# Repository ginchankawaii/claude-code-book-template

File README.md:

# 🧪 ENCOR合格ストーリー 〜タキと目指す9月合格〜

CCNP ENCOR(350-401)に**2026年9月(上期末)合格**するための、ギャルゲー風・学習継続アプリです。
毎日の勉強を記録すると、検証ラボの同期・**早瀬タキ**(ツンデレ天才研究者)の好感度が上がり、レベルアップでイベントが発生。合格報告でハッピーエンドを迎えます。

> タキ『べ、別にキミのためにこのアプリがあるわけじゃないんだからね。……データが欲しいだけさ』

## 📱 iPhoneにアプリとして入れる方法(PWA)

このアプリはPWA対応済みなので、ホーム画面に追加すると**普通のアプリと同じように全画面・オフラインで動きます**。

1. このリポジトリをGitHub Pagesで公開する(初回のみ)
   - GitHubの **Settings → Pages → Branch: main → Save**
   - 数分後に `https://<ユーザー名>.github.io/<リポジトリ名>/` でアクセスできるようになる
2. iPhoneの**Safari**でそのURLを開く
3. **共有ボタン(□↑) → 「ホーム画面に追加」**
4. ホーム画面にタキのアイコンが追加される → 以降はアプリとして起動🧪

データはブラウザ(ホーム画面アプリ)内に保存されます。月1回「データ書き出し」でJSONバックアップ推奨。

※PCで使う場合は `index.html` をダブルクリックするだけでも動きます。

## 🎮 ゲームシステム

| 要素 | 内容 |
|---|---|
| 好感度 (0〜100) | 毎日の記録で上昇。30分以上・40問以上・正答率80%以上・7日連続でボーナス |
| レベル | Lv.1 観察対象 → Lv.2 共同研究者 → Lv.3 興味深いキミ → Lv.4 かけがえのない相棒 → Lv.5 運命共同体(たぶん) |
| イベント | レベルアップ時・連続7/14/30日達成時に特別イベント発生 |
| 表情 | ドット絵4表情: ニヤリ(通常)・デレ・キラキラ・ツン(サボると拗ねる) |
| キャラ差し替え | 好きな二次元画像(生成AI画像など)をキャラとして設定可能 |
| 復帰歓迎 | 3日以上サボっても「心配なんかしてない」と言いながら迎えてくれます |
| ハッピーエンド | 「合格しました!!」ボタンでツンデレ告白エンド 🌸(下期ENARSI編に続く) |

## 👩‍🔬 早瀬タキ(はやせ・タキ)

会社の検証ラボに入り浸る同期の天才エンジニア。白衣・栗色の乱れ髪・深紅の目・胸ポケットに試験管。
一人称「私」、キミ呼び。勉強を「実験」、記録を「データ提出」と呼ぶ。素直じゃないが、誰よりもキミの合格を信じている。

**キャラはドット絵(4表情)で描画されます。** もっと可愛くしたい場合は「🖼 キャラ画像に差し替え」ボタンで、
生成AI(にじジャーニー等)で作った画像や好きな二次元画像に差し替えられます(画像は端末内にのみ保存)。

## 📖 ドキュメント

- [docs/study-plan.md](docs/study-plan.md) — 7〜9月の週次学習計画・1日のルーチン・if-thenルール・モチベーション維持の仕組み
- [docs/simulation.md](docs/simulation.md) — ENCORシミュレーション(ラボ)問題の対策メモ・頻出設定テーマ・本番の立ち回り
- [docs/ipoe-lab/](docs/ipoe-lab/README.md) — PPPoE→IPoE切替検証ラボ(VMware)の設計・構築手順・検証マトリクス(業務用)

## 🗺️ 合格までのロードマップ

```
7月         8月         9月
├─ 銀メダル化 ─┼─ 金メダル化 ─┼─ 模試+シミュ対策 ─→ 🌸受験🌸
   (二周目)     (+コマ問)      (85〜90%安定で予約)
```

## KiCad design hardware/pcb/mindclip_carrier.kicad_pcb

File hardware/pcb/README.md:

# MindClip DIY — 基板（PCB）設計

**結論から: v1 では基板を作らない。** 4案を設計・比較し、3人の審査員が独立採点した結果、
**「基板を起こさず、空中配線を改良する」案が採用**された。ただし検討は無駄にならず、
v1 の設計が **はんだ11点 → 10点** に減り、**電池の極性事故リスクが下がった**（JSTコネクタ化）。
（v1.8 rev2〜v1.10 ではピグテールの線を細い AWG28 に継ぎ足す 2点があり 12点だったが、採用ピグテールの線は実測 0.90mm と細く
そのまま使えるため v1.11 で廃止した。**現在の作業は 10点（線が太いピグテールで継ぎ足す場合のみ +2）**。
電池側のコネクタは **1.25mm ピッチ 2P** と確定した。正本は [`SCHEMATIC.md`](SCHEMATIC.md) §0.1 / §1.4。）
**v2用の基板 2種（MC-SENSE-A / MC-CARRIER-A）は、現在の筐体（v1.8、内寸幅 36.8mm・実測スイッチ）には
どちらも合わず、筐体 CAD でも実行できない**（[`LAYOUT.md`](LAYOUT.md) §0 冒頭）。
将来 v2 で基板が必要になったときのために、**発注可能な基板データも作って置いてある**。

- 採用構成の詳細 → [`SCHEMATIC.md`](SCHEMATIC.md)（回路・ネットリスト・テスタゲート）
- v2用の基板データ → [`LAYOUT.md`](LAYOUT.md) §0 を**必ず先に読むこと**
- 組み立て手順 → [`../README.md`](../README.md)

---

## 1. なぜ基板を作らないのか

### 1.1 高さ予算が足りない

筐体CAD（`../cad/mindclip_case.py`）を実行して実測した、基板を入れられる余地:

| バリアント | 高さ予算 | 1.6mm厚基板 | 0.8mm厚基板 |
|---|---|---|---|
| allday | **2.30 mm** | 入る（ただし余裕0.7mm） | 入る |
| slim | **0.60 mm** | **入らない** | **入らない**（はんだフィレット+固定材で超過） |

**slim バリアントは、どんな基板を入れても原理的に成立しない。** 基板を採用すると
2バリアント体制を捨てるか、筐体を作り直すことになる。

### 1.2 寸法がまだ実測されていない

より本質的な理由。`../README.md` §9.1 に列挙した**未検証の寸法が1つも実測されていない**:

- XIAOスタックの総厚 **7.5mm（assumption）** ← slim の内寸9.5mmはこの値に直接依存
- マイクの基板上の位置、XIAO裏面BATパッドの正確な位置
- 802530電池の実寸、USB-Cケーブルの嵌合

もし実測でスタック厚が 8.3mm だったら、slim の内寸は即破綻する。
**基板は「寸法が固まった後の最適化」であって、「寸法を固める手段」ではない。**
この状態で基板を焼くと、失敗コストが「2週間の納期 + ¥4,700 + XIAO ¥2,660」になる。

### 1.3 反復コストの差

| | 設計ミスに気づいてから直るまで |
|---|---|
| 空中配線 | **その晩**（線を1本付け替える） |
| 基板 | **2週間**（再発注） |

ファームウェアがまだ存在せず、VBUS検出のGPIO選定・分圧比・ADC校正を
「回路を触りながら詰める」段階では、この差が決定的に効く。

---

## 2. 4案の比較

| | 案A **採用** | 案B | 案C | 案D |
|---|---|---|---|---|
| 構成 | 基板なし・空中配線改良 | キャリア基板（直はんだ） | キャリア基板＋ソケット | ユニバーサル基板手組み |
| 追加高さ | **0 mm** | +1.0 mm | **+7.1 mm** | 0 mm |
| 手はんだ | **10点** | 20点 | **54点** | 36点 |
| 費用 | ¥1,100 | ¥4,700 | ¥1,400 | ¥310 |
| 納期 | **即日** | 2週間 | 3週間 | 即日 |
| VBUS検出 | ✗ | ✓ | ✓ | ✓ |
| 電池監視 | ✗ | ✓ | ✓ | ✓ |
| 採点合計 | **174** | 132 | 42 | 79 |

審査員の推し: 組立性→**案A** / 機構→**案A** / 電気→**案B**

### 不採用の理由

- **案B（キャリア基板）**: 設計としては最も筋が良く、**v2 で作るならこれ**。
  ただし今作ると 1.2 の「寸法未実測」に直撃する。また目的の一つだった
  「電池直はんだの排除」は達成できない（BATパッドが基板裏面にあるため窓＋ジャンパが残る）。
  手はんだも 11→20点と**増える**。
- **案C（ソケット式）**: 却下。外形が +4.6mm（14.6→19.2mm）、手はんだ54点、slim消滅。
  「XIAOを壊しても差し替えられる」という唯一の価値も、BAT+/−がヘッダに出ていないため
  成立しない。**予備のXIAOを1枚買う（¥2,660・即日）ほうが安くて確実。**
- **案D（ユニバーサル基板）**: 「まず1台試す」段階の現実解ではあるが、
  再現性とドキュメント化に耐えない（24穴中19穴に詰め込み、手はんだ36点）。

---

## 3. 検討の結果、v1 に反映されたこと

基板を作らないと決めた一方で、**案Aの改良（A-1）は v1 に取り込んだ**:

| | 変更前 (v1) | 変更後 (v1.5) |
|---|---|---|
| 電池の接続 | BATパッドに**直はんだ** | **JST ピグテール**（コネクタ嵌合。電池側プラグと同じ **1.25mm ピッチ 2P**。当初の「PH2.0」指定は誤りで訂正済み） |
| GND配線 | 空中で3本より合わせ（スプライス） | **デイジーチェーン**（スプライス廃止） |
| はんだ点数 | 11点 | **10点**（線が太いピグテールで継ぎ足す場合のみ +2。v1.8 rev2〜v1.10 は継ぎ足しが標準で 12点だった） |
| 電池リード長 | 未指定 | ピグテールを根元から約 60 / 65mm の長さ違いに切ってそのまま使う（v1.11。v1.5 時点は「40mm 指定」、v1.8 rev2〜v1.10 は「10 / 15mm で切って AWG28 55mm を継ぐ」） |

**JSTコネクタ化の効果**: 電池を「挿す」作業に変わるので、はんだごてを持ったまま
極性を間違える事故が減る。加えて、電池だけ後から外せるので保管・輸送も安全になる。

> **ただし極性リスクはゼロにならない。** JSTの極性キーは「上下逆挿し」しか防がず、
> **ハウジング内のコンタクト位置が逆に配線された電池（中華セルに実在）は防げない**。
> `SCHEMATIC.md` §5.4 の**嵌合前テスタゲートは必須のまま**。組立ガイドの手順8に
> 「リード線の色を信用せず、コンタクト位置で極性を測る」手順として組み込んである。

---

## 4. v2用の基板データ（発注しないこと）

将来のために、2種類の基板を設計してガーバーまで出力してある。

| 基板 | 外形 | 用途 |
|---|---|---|
| `mindclip_sense.kicad_pcb` | 10.0 × 15.6 mm | サテライト基板。VBUS検出＋電池監視だけを載せる最小構成 |
| `mindclip_carrier.kicad_pcb` | 34.2 × 21.5 mm | キャリア基板。XIAOをカステレーション直はんだ |

**発注してよいのは、以下のゲートを全て通過してからである**（`SCHEMATIC.md` §9.4）:

1. v1 を1台組んで、消費電流ゲート（平均 ≤28mA）を通す
2. **ノギスでXIAOスタック総厚を実測**し、`XIAO_STACK_T` を更新
3. XIAO裏面 BAT+/− パッドの座標を実測
4. 802530の実寸・リード出射方向・JSTプラグ極性を確認
5. `gen_pcb.py` を再実行して DRC を通す

### 検証状況（正直に）

- ✅ 独立ジオメトリDRC **エラー0件**。設計途中で見つかった**異ネット衝突41件
  （うち銅箔レベルの直短絡16件）は修正済み**で、独立検証でも0件を確認した
- ❌ **KiCad本体のDRCは一度も走っていない**（この環境にKiCadが無いため）
- ❌ 製造業者のDFMチェックも未実施
- ❌ 逆接続保護FETは MC-CARRIER-A rev.A には**載っていない**

発注前に必ず KiCad で開いて DRC を通すこと（手順は `LAYOUT.md` §9.3）。

---

## 5. 基板を作るべき条件

以下のどれかに当てはまったら、案B（キャリア基板）に移行する:

1. 実測でXIAOスタック厚が 7.5mm を明確に**下回った**（高さ予算に余裕ができる）
2. **3台以上作る** / 他人に作らせる / 書籍の作例にする
3. **VBUS検出**（充電開始をトリガに自動同期）が必須要件に昇格した
4. 極性ミスによる破損を**設計で排除する**ことが要件になった

3番は全体設計書の「充電ドックに置いたら同期開始」に対応する。
v1 ではこの回路が無いため、**同期のトリガはスライドスイッチOFFのみ**である。

---

## 6. ファイル一覧

| ファイル | 内容 |
|---|---|
| `SCHEMATIC.md` | 回路設計・ネットリスト・テスタゲート（**採用案A-1の正本**） |
| `LAYOUT.md` | 基板レイアウト仕様・製造仕様・発注手順 |
| `OPTION_A〜D_*.md` | 4案それぞれの詳細検討 |
| `netlist.json` | 機械可読ネットリスト |
| `gen_pcb.py` | ネットリストから `.kicad_pcb` とガーバーを生成 |
| `schematic.svg` / `layout.png` | 回路図・部品配置図 |
| `gerber/` | 製造用データ（**ゲート通過前は発注不可**） |

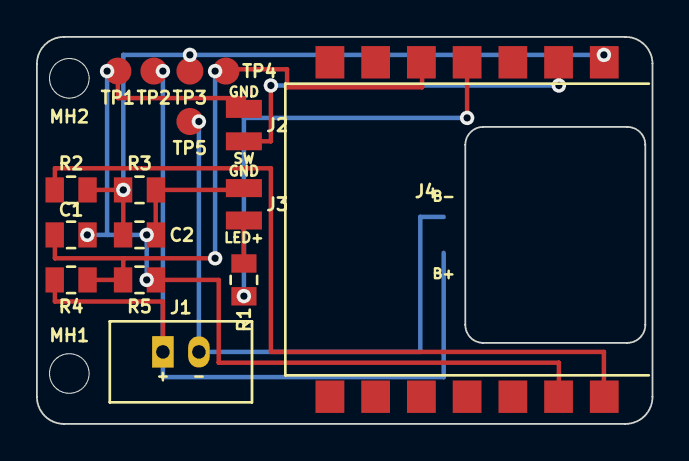
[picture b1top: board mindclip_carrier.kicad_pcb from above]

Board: 2 copper layers, 34.2 x 21.5 mm, 19 parts (0 on the bottom side), 9 nets.

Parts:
C1, C2: 100nF; C_0805_2012Metric_MC
J1: JST_PH_2P; JST_PH_B2B-PH-K_1x02_P2.00mm_Vertical_MC
J2, J3, J4: WIRE x2; WireLand_SMD
MH1, MH2: MountingHole_2.2mm; MountingHole_2.2mm_M2_MC
R1: 220R; R_0805_2012Metric_MC
R2, R4, R5: 220k; R_0805_2012Metric_MC
R3: 330k; R_0805_2012Metric_MC
TP1, TP2, TP3, TP4, TP5: TP; TestPoint_Pad_D1.5mm_MC
U1: XIAO ESP32S3 Sense; XIAO_ESP32S3_Castellated_2x7_P2.54mm

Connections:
BATN: J1.2, J4.2, TP5.1
BATP: J1.1, J4.1, R4.1, TP2.1
GND: C1.2, C2.2, J2.2, J3.2, R3.2, R5.2, TP1.1, U1.GND
LED_A: J3.1, R1.2
LED_DRV: R1.1, U1.D3
SW_IN: J2.1, U1.D1
VBAT_SENSE: C1.1, R4.2, R5.1, TP4.1, U1.D4
VBUS: R2.1, U1.5V
VBUS_SENSE: C2.1, R2.2, R3.1, TP3.1, U1.D0

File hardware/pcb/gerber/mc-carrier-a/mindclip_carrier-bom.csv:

Comment,Designator,Footprint,LCSC Part #
"100nF","C1,C2","MindClip:C_0805_2012Metric_MC",
"220R","R1","MindClip:R_0805_2012Metric_MC",
"220k","R2,R4,R5","MindClip:R_0805_2012Metric_MC",
"330k","R3","MindClip:R_0805_2012Metric_MC",
"JST_PH_2P","J1","MindClip:JST_PH_B2B-PH-K_1x02_P2.00mm_Vertical_MC",
"WIRE x2","J2,J3,J4","MindClip:WireLand_SMD",
# LCSC Part # は未指定。JLCPCB の SMT 実装を使う場合は発注前に記入すること。
# 本プロジェクトの既定は手はんだ（0805 まで）なので実装サービスは任意。

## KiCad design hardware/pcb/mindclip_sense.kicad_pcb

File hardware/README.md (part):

# MindClip DIY — 組み立てガイド（電子工作がはじめての人向け）

自作ウェアラブル音声ロガー **MindClip DIY** のハードウェアを、
**電子工作がまったく未経験の人でも、この手順どおりにやれば組める**ように書いたガイドです。

> **この文書が「正」です。** `ELECTRICAL.md` / `MECHANICAL.md` / `bom.md` と食い違いがある場合は
> このREADMEの記述を優先してください（矛盾していた箇所は各ファイル側も修正済みです）。

---

## 目次

1. [これは何か](#1-これは何か)
2. [完成品の外観](#2-完成品の外観)
3. [バリアントの選び方](#3-バリアントの選び方)
4. [必要な工具一覧](#4-必要な工具一覧)
5. [部品の購入](#5-部品の購入)
6. [3Dプリント手順](#6-3dプリント手順)
7. [組み立て手順](#7-組み立て手順)
8. [動作確認](#8-動作確認)
9. [既知の課題・未検証事項](#9-既知の課題未検証事項)

---

## 0. 最初に読む安全上の注意

作業を始める前に、これだけは頭に入れてください。

- **リチウムポリマー（LiPo）電池は、ショート・逆接続・穴あけで発火します。** 必ず保護回路（PCM）付きを買い、
  被覆を剥いた＋と−のリード線を絶対に触れ合わせないでください（[§7 手順8](#手順8-電池をつなぐjstコネクタ-最重要)）。
- **電池の極性を間違えると、XIAO（¥2,660）は一瞬で壊れます。** 復旧できません。
  v1.5 では電池を **JST コネクタ（電池に付いているプラグと同じ 1.25mm ピッチ 2ピン）で嵌合**する方式に変えましたが、
  **コネクタは「上下逆挿し」しか防いでくれません**（中身の赤黒が逆の個体、
  ハウジング内のコンタクト位置が逆の個体が実在します）。
  **嵌合の前に、テスターで4項目を確認する手順（手順8-B）が唯一の防御です。省略しないでください。**
- **電池のプラグの穴に、テスターの棒・針金・クリップなどの金属を差し込まないでください。**
  1.25mm ピッチのコンタクトは隣どうしが 1mm も離れておらず、金属が斜めに入っただけでショートします。
  電池側の電圧を測るときは、必ず**予備のピグテールを挿して、その線の先で測ります**（[手順5](#手順5-電池ピグテールjstの準備と極性の測定はんだ-0か所)・手順8-B）。
- **電池が繋がっている間は、被覆を剥いた電線の先を2本同時に自由にしない。**
  1本ずつテープで包むか、2本を3cm以上離して机にテープで留めてから作業します。
- はんだごてのこて先は **300℃以上**です。触れると重度のやけどをします。使わないときは必ずこて台に置く。
- はんだの煙は吸わない。**必ず換気**してください（窓を開ける、換気扇を回す）。
- 完成後、**microSDカードやクレジットカード・磁気定期券と密着させて持ち歩かない**でください
  （本機は背面にネオジム磁石を内蔵しています）。

---

## 1. これは何か

MindClip DIY は、襟元にクリップで留めて日常会話を録音し、
そのデータを**自宅のローカルサーバだけ**で文字起こし・要約して Obsidian の Daily Note に貯める、
「外部クラウドに一切データを出さない」音声ライフログデバイスの**自作ハードウェア（Phase 1）**です。
心臓部は Seeed Studio の小型マイコンボード **XIAO ESP32S3 Sense**（マイクとmicroSDスロットが載った拡張ボード付き）で、
外付け部品は **電池・スライドスイッチ・LED（+抵抗）の3つだけ**、はんだ付けは**合計10か所**です
（v1.5 で電池を JST コネクタ化し、空中での3本より合わせを廃止しました。
採用したコネクタ付きコードの線は細く、そのまま使えます。線が太い別のコードで継ぎ足す場合のみ +2か所）。
システム全体の考え方は [`../docs/local-llm-voice-logger-design.md`](../docs/local-llm-voice-logger-design.md)、
すでに動いている録音ファイル→Obsidian のパイプライン（Phase 0）は [`../voice-logger/`](../voice-logger/) にあります。
**このデバイスのファームウェアは実装済みです** → [`../firmware/`](../firmware/README.md)
（書き込み・WiFi設定・実測ゲートの手順はそちらのガイドにあります）。
本ガイドのゴールは「筐体と回路が正しく組み上がり、マイク・SD・スイッチ・LEDが動くことを確認したうえで、
[§8](#8-動作確認) でファームを焼いて録音〜サーバ同期まで通す」ところまでです。

---

## 2. 完成品の外観

以下は CAD（[`cad/mindclip_case.py`](cad/mindclip_case.py)）が自動生成したレンダリング画像です
（**allday バリアント**のもの。slim は [`renders/slim/`](renders/slim/) にあります）。

| 組み立て状態 | 分解図 |
|---|---|
|  |  |
| 服を挟んで、本体（手前）と裏板（服の内側）を磁石でクランプする | 上から リッド / 本体 / 磁石2個 / 裏板 / 磁石2個 |

| 三面図（寸法入り） | 内部レイアウト |
|---|---|
|  |  |
| 上面にマイク穴とスイッチ、右側面にUSB-C | 下段に電池、上段にXIAO、左にスイッチとLED |

- [`renders/allday/assembled.png`](renders/allday/assembled.png)
- [`renders/allday/exploded.png`](renders/allday/exploded.png)
- [`renders/allday/views.png`](renders/allday/views.png)
- [`renders/allday/internal.png`](renders/allday/internal.png)

配線の全体像は [`wiring.svg`](wiring.svg)（ブラウザで開いてください）が一番わかりやすいです。
**印刷して手元に置きながら作業する**ことを強く勧めます。

---

## 3. バリアントの選び方

筐体CADは **allday** と **slim** の2種類を出力できます。違いは**電池の厚みと、それに伴う筐体の奥行きだけ**です。
回路・配線・はんだ付け・部品点数は完全に同じです。

### allday（既定・**こちらを推奨**）

| 項目 | 値 |
|---|---|
| 電池 | **LiPo 802530（3.7V 680mAh、実測 32.0×25.0×8.0mm・11g、保護回路付き、コネクタは 1.25mm ピッチ 2ピン。採用品: HXJNLDC、[`bom.md`](bom.md) #2）** |
| 外形 | **40.0 × 49.4 × 14.6 mm**（v1.8 実測反映） |
| 印刷部品の重量 | 15.9 g（body 8.2 / lid 4.8 / backplate 2.9） |
| デバイス総重量 | **約35 g**（電池は実測 11g。[§9](#9-既知の課題未検証事項)の注記も参照） |
| 素の状態（省電力実装なし）の連続録音 | **約10.6時間** |
| 生成コマンド | `python3 cad/mindclip_case.py` |

### slim

| 項目 | 値 |
|---|---|
| 電池 | LiPo 502530（3.7V 500mAh、30×25×5.0mm、保護回路付き） |
| 外形 | **40.0 × 49.4 × 13.7 mm**（v1.11 実測反映） |
| 印刷部品の重量 | 15.7 g（body 7.9 / lid 5.0 / backplate 2.9） |
| デバイス総重量 | 約34 g（電池を公称 10g とした見積） |
| 素の状態（省電力実装なし）の連続録音 | 約7.8時間 |
| 生成コマンド | `MINDCLIP_VARIANT=slim python3 cad/mindclip_case.py` |

### なぜ allday を既定にしたか

Seeed公式スペック表に載っている**実測値**「Microphone recording & SD card writing = 3.8V / 平均54.4mA・ピーク108mA」を
電力予算の基準（＝最悪ケース）に置くと、こうなります。

| バリアント | 公称容量 | 実効容量（×0.85） | ÷ 54.4mA |
|---|---|---|---|
| slim | 500mAh | 425mAh | **約7.8時間** |
| allday | 680mAh | 578mAh | **約10.6時間** |

「起床から就寝まで（約15時間）」を目標にすると、**どちらのバリアントも素の状態では届きません**。
allday でも worst case は10.6時間ですが、ファームウェア側の省電力
（CPUクロックを240MHz→80MHzに下げる／SDへの書き込みをRAMにためてまとめ書きする／
無音を検出して書き込みを止める VAD ゲート）で**平均28mAの目標（[§8.7](#87-テスト6-消費電流の実測ゲート必須)）を達成すれば約20.6時間**が見込めます。

そして厚みの増加は **0.9mm だけ**です（14.6mm と 13.7mm）。電池は 5.0mm → 8.0mm と3mm厚くなりますが、
slim の奥行きは XIAO のスタック（基板＋拡張ボード、実測 8.3mm）が決めているので、電池の差がそのまま外形には出ません。
**この0.9mmと引き換えに録音時間が約1.4倍になるので、迷ったら allday** を選んでください。

> **slim を選ぶ理由があるとすれば**: 「とにかく薄くしたい」「会議の1〜2時間だけ使えればいい」場合です。

> **重要な注意（充電時間）**: XIAO の充電電流は **50mA固定**です。680mAh を空から満充電にするには
> **15〜16時間**かかります（500mAhでも11〜12時間）。つまり **一晩（10時間）の充電で戻せるのは約500mAh**。
> allday の 680mAh は「1日にたくさん使うための容量」ではなく、**省電力実装が間に合うまでのマージン・
> 充電し忘れた日の余力・経年劣化代**として効きます。詳しくは [§9](#9-既知の課題未検証事項)。

---

## 4. 必要な工具一覧

「何を買えばいいかわからない」を無くすため、**用途・価格・選び方**をすべて書きます。

### 4.1 これは必ず要る（合計 ¥8,000〜12,000程度）

| # | 工具 | 何に使うか | 目安価格 | 選び方・入手先 |
|---|---|---|---|---|
| T1 | **はんだごて**（30W前後） | 10か所のはんだ付け全部 | ¥1,500〜6,000 | 安く済ませるなら goot KS-30R 等の固定温度30W（¥1,500）。**温度調節付き（白光 FX-600 / ¥6,000前後）だと失敗が激減する**ので、今後も電子工作をするなら最初から温調付きを勧めます。こて先は**細めのB型（φ2mm前後）かC型**。極細（φ0.5）は熱が足りず初心者には難しい。秋月電子・Amazon |
| T2 | **こて台**（クリーニング用スポンジ or ワイヤ付き） | こてを安全に置く／こて先を掃除する | ¥800〜1,500 | 白光 FH-300 など。**「机に直置き」は火事とやけどの原因なので絶対にやらない**。ワイヤ（金だわし）タイプの方がこて先温度が下がらず良い |
| T3 | **はんだ**（φ0.6mm ヤニ入り） | 同上 | ¥800〜1,500 | **初心者は鉛入り（Sn60/Pb40）を強く推奨**。融点が約183℃と低く、格段に扱いやすい。鉛フリーは融点217℃で難易度が上がります。太さは**φ0.6mm**（φ1.0は今回の細かい作業には太すぎ）。作業後は手を洗う |
| T4 | **はんだ吸い取り線**（φ2mm） | **失敗のやり直し**。付けすぎたはんだ、ブリッジ（隣同士がくっつく）の除去 | ¥300〜600 | goot CP-2015 等。**これが無いと失敗がリカバリできません。必ず買ってください** |
| T5 | **ワイヤストリッパ** | AWG28〜30の細い電線の被覆を剥く | ¥1,200〜2,500 | **AWG30まで対応**の表記があるものを選ぶ（例: エンジニア PA-06、ベッセル No.3500E-1）。ニッパーやカッターで剥くと芯線を切ってしまい、後で断線します |
| T6 | **ニッパー**（精密用・小型） | 電線・部品リードの切断 | ¥1,000〜2,500 | HOZAN N-31、フジ矢 等。工作用の大きいニッパーだと細かい所に入りません |
| T7 | **ピンセット**（先の細いストレート） | 小さい部品・電線を押さえる。**熱い部品を触らない**ためにも必須 | ¥300〜1,500 | ステンレス製の先細（No.5型）。100円ショップのものでも可だが、先がぴったり合うものを |
| T8 | **テスター（デジタルマルチメータ）** | **電池の極性確認**（これを怠ると基板が壊れる）／ショートしていないかの導通確認／電圧測定 | ¥1,500〜3,000 | **「導通ブザー機能」と「DC電圧測定」があれば十分**。Amazon の安価品でOK。**この工具だけは省略不可** |
| T9 | **USB Type-C 電流・電圧チェッカー** | [§8.7 の消費電流の実測ゲート](#87-テスト6-消費電流の実測ゲート必須)。充電できているかの確認にも使う | ¥1,000〜2,500 | 「USBテスター Type-C 電流計」で検索。**積算容量（mAh）表示があるもの**が測定に便利 |
| T10 | **USB-Cケーブル**（データ通信対応） | ファーム書き込み・充電 | ¥0〜1,000 | **「充電専用」ケーブルはPCから認識されません。**必ずデータ通信対応品を。手持ち流用可 |
| T11 | **ライター or ヒートガン** | 熱収縮チューブを縮める | ¥100〜3,000 | ライターで可（**炎を直接当てず、横のあぶりで**。当てすぎると溶けて穴が開く）。ヒートガンがあれば確実。**電池のそばではライターを使いません**（電池を出している間は火を使わない） |
| T12 | **耐熱マット or 作業板**（不要な板・タイル等） | 机を溶かさない・焦がさない | ¥0〜1,000 | ダンボールは焦げるので避ける。100円ショップの陶器タイルでも可 |

### 4.2 あると成功率が上がる（推奨）

| # | 工具 | 何に使うか | 目安価格 |
|---|---|---|---|
| T13 | **「第三の手」（ヘルピングツール）** | 基板や電線をクリップで固定する。片手にこて・片手にはんだだと**部品を持つ手が足りない**ので、実質必須に近い | ¥800〜2,500 |
| T14 | **フラックス**（ペーストまたはペン） | はんだの乗りが悪いパッド（XIAO裏面のBATパッドなど）に塗ると劇的に楽になる | ¥500〜1,000 |
| T15 | **ノギス** | 印刷した筐体・買った電池の実寸確認（[§9](#9-既知の課題未検証事項)の未検証項目の検証に使う） | ¥1,000〜2,500 |
| T16 | **針ヤスリ（丸・平）／紙ヤスリ #400** | スナップフィットの嵌合調整、磁石ポケットの微調整 | ¥500〜1,000 |
| T17 | **カッターナイフ・デザインナイフ** | 3Dプリントのバリ取り、糸引きの除去 | ¥300〜800 |
| T18 | **静電気防止リストバンド** | 冬場の基板保護。無い場合は**作業前に金属（ドアノブ等）に触れて放電**する | ¥500〜1,000 |

### 4.3 3Dプリンタ

- **自分で持っている場合**: FDM機（Bambu Lab / Prusa / Ender 等）で十分です。[§6](#6-3dプリント手順)へ。
- **持っていない場合**: STLファイルを外部サービスに投げます。
  - 個人向け: **DMM.make 3Dプリント**、**JLCPCB 3D Printing**（安価だが海外発送）
  - 近所のファブラボ・メイカースペース・図書館のデジタル工房（1時間数百円で使えることが多い）
  - **PETGを指定できるサービスを選んでください**（理由は[§6](#6-3dプリント手順)）。

### 4.4 買い物メモ（最短ルート）

秋月電子で **T1（こて）・T2（こて台）・T3（はんだ）・T4（吸い取り線）・T5〜T7** と[§5](#5-部品の購入)の電子部品をまとめて注文し、
**T8（テスター）・T9（USB電流計）・T13（第三の手）** を Amazon で買うのが手数が少ないです。

---

## 5. 部品の購入

**部品表の正本は [`bom.md`](bom.md) です。** ここでは「買うときにハマりやすい点」だけを説明します。

### 5.1 買い物リスト（要点だけ）

| # | 部品 | 個数 | 目安 | 入手先 |
|---|---|---|---|---|
| 1 | Seeed Studio **XIAO ESP32S3 Sense** | 1 | ¥2,660 | 秋月 通販コード **118079** |
| 2 | **LiPo電池**（バリアントによる。下記5.2） | 1 | ¥900〜1,500 | Amazon 等 |
| 3 | **microSDカード 32GB**（下記5.3） | 1 | ¥800 | Amazon 等 |
| 4 | スライドスイッチ SS-12D00G3 | 1 | ¥20 | 秋月 通販コード **115707** |
| 5 | 3mm 赤色LED（OSR5JA3Z74A） | 1 | ¥10〜20 | 秋月 通販コード **111577** |
| 6 | カーボン抵抗 **220Ω 1/4W** | 1 | ¥200/100本 | 秋月 通販コード **125221** |
| 7 | 配線材 **AWG28**（赤・黒・青・橙。住友電工 イラックスA） | 各20cm以上 | ¥300 | 秋月 通販コード **111640** / 手持ち |
| 8 | 熱収縮チューブ **φ3mm**（φ1.5mm は外径1.5mmの線に通らないので不可） | 1式 | ¥200〜500 | 秋月 通販コード **106789** / Amazon |
| 9 | ポリイミド（カプトン）テープ 幅10mm | 1巻 | ¥500 | Amazon |
| 9a | 薄手両面テープ ＋ 1mm厚スポンジ | 1式 | ¥300〜500 | Amazon / 100円ショップ |
| 9b | **2液エポキシ接着剤** | 1 | ¥300 | ホームセンター / 100円ショップ |
| 9c | ホットボンド or 多用途接着剤 | 1式 | ¥100〜500 | 100円ショップ |
| **A1** | **JST 1.25mm 2ピン コネクタ付きコード（ピグテール／オス・メス組）**。**電池のプラグと同じ系統のもの**（下の注記） | 1組（実際は複数組入りで売られている） | ¥300〜600 | 楽天 / Amazon |
| 10 | ネオジム磁石 **φ6 × 厚2mm** | **4個** | ¥300〜500 | Amazon / 100円ショップ |
| 11 | PETGフィラメント | — | ¥500相当 | — |

**デバイス本体の合計: 約 ¥6,800〜8,100**（工具を除く）。

> **#A1（JST ピグテール）は v1.5 で追加した部品です。** これが無いと
> [手順8](#手順8-電池をつなぐjstコネクタ-最重要) が組めず、v1 の「電池を基板に直はんだ」に
> 逆戻りします。
>
> **【一度まちがえて買っています】** 採用電池（HXJNLDC 802530）のプラグは **1.25mm ピッチの 2ピン**
> （メーカー仕様表の表記は「1.25-2P」）です。最初に買ったピグテール（SONONIA B076SSLHHL）は
> 商品名こそ「1.25mm」でしたが、届いた現物は 2.0mm 系で電池に挿さりませんでした。
> **「1.25mm」と書かれたコネクタには、互いに挿さらない複数の系統があります**（見た目はそっくりです）。
> 現在の購入品は **「JST 1.25mm 15cm 2ピン オス＆メス 20ペア」**（楽天・Coolotic 系）で、
> **採用電池に軽い力で挿さることを現物で確認済み**です（嵌合体の実測 長さ 9.2 × 幅 4.2 × 厚み 3.3mm、
> 線の外径 0.90mm。[`MEASUREMENTS.md`](MEASUREMENTS.md) M4・M5）。筐体（v1.11）はこの品に合わせてあります。
>
> 買うとき・届いたときの条件:
> 1. **圧着済み（プリクリンプ）品**であること。「コネクタ付きケーブル」「配線済み」の表記のもの。
>    ハウジングと端子だけのセットは圧着工具（¥3,000〜）が要るので買わないこと。
> 2. **オス・メス組**を買う。どちらが電池と嵌合するかは現物を合わせるまで確定しません。
>    余ったほうは、手順8-B の測定用として必ず使います（捨てない）。
> 3. **合格の判定は商品名ではなく現物で行います**: ①電池のプラグの**隣に並べて**、幅・ピンの間隔・
>    ツメの形が同じか見比べる → ②**指先の軽い力で**まっすぐ挿してみる。
>    **軽い力で奥まで入らないものは系統違いです。押し込まない・こじらない**
>    （やり方と注意は [手順5](#手順5-電池ピグテールjstの準備と極性の測定はんだ-0か所) の 5-1）。
> 4. **電線は細いもの（被覆込みの外径が 1.3mm 以下）を選びます。** XIAO の裏面には 1.40mm の隙間しかなく、
>    それより太い線は通せません。**上の購入品は実測 0.90mm で、そのまま使えます**（継ぎ足し不要）。
>    別の品で線が 1.3mm を超える場合は細い線への継ぎ足しが必要になりますが、今の筐体には継ぎ目の置き場所が
>    無いので、**買い直すか、相談してください**（[手順5](#手順5-電池ピグテールjstの準備と極性の測定はんだ-0か所) の囲み）。

### 5.2 【最重要】LiPo電池の買い方

- **必ず「保護回路（PCM / PCB / 保護基板）内蔵」と明記されたものを買ってください。**
  XIAO に載っている充電IC（TI BQ25101）は**充電の制御しかしません**。過放電・過電流・短絡から
  電池を守る回路は入っていないので、**電池側の保護回路が唯一の安全装置**です。
  保護回路なしのセル（ラジコン用の「裸セル」など）を使うと、過放電で電池が死ぬ／最悪発火します。
- **サイズは型番がそのまま寸法です**（例: 802530 = 厚8.0 × 幅25 × 長30 mm。ただし採用品の実測は全長 32.0mm。筐体は 32.0×25.0×8.0 に合わせてあり、**長さ33.0mm・幅25.3mm・厚さ8.5mm を超える個体は入りません**）。
  **容量は型番に含まれません** — 802530 の実容量は約680mAhで、「800mAh」を名乗る 802530 は
  物理的に不可能な密度です（[`bom.md`](bom.md) のエネルギー密度検算を参照）。
  - allday を作る → **802530（680mAh。採用品は [`bom.md`](bom.md) #2 の HXJNLDC）**
  - slim を作る → **502530（500mAh）**
  - **厚みは公称+0.5mmまで**（allday は 8.5mm 超、slim は 5.5mm 超の個体は筐体に入りません）。
- **放電能力**: 連続500mA（1C）以上・瞬時1A程度を許容する保護回路であること。
  WiFi送信時に瞬間的に300mAを超えるためです。市販の一般的な保護回路（2A級）なら通常満たしますが、商品説明を確認してください。
- **【v1.5 必須】コネクタ（プラグ）が付いているもの**を買ってください。
  採用品（HXJNLDC 802530）のプラグは **1.25mm ピッチの 2ピン**です。
  v1 では「コネクタは切り落として使う」と書いていましたが、**この記述は撤回します。**
  v1.5 以降は #A1 のピグテールと嵌合させる前提で、切り落とすと直はんだ（v1）に逆戻りし、
  **充電済みの電池を持ったまま基板にこてを当てる**という一番危ない作業が復活します。
  - **ピグテール（#A1）は「電池に付いているプラグ」に合わせて買います**（逆ではありません）。
    商品説明の「1.25mm」「2.0mm（PH）」「GH」「SH 1.0」「XH 2.5」はすべて別物で、
    **同じ「1.25mm」どうしでも系統が違えば挿さりません**。
    合っているかどうかは、**電池のプラグの隣に並べて見比べ、指先の軽い力で挿さるか**でしか判定できません
    （[§5.1](#51-買い物リスト要点だけ) の #A1 の注記）。
  - **もしバラ線（コネクタ無し）の電池が届いてしまったら**:
    ①返品・交換が最優先。②どうしても使う場合は、**電池側のリードにピグテールを
    はんだ付けする**ことになります（＝充電済みセルへの通電はんだ 2点増。
    必ず1本ずつ・被覆を同時に剥かない・こては2秒以内。**初心者には勧めません**）。
  - 電池に XH(2.5mm) など大きいプラグが付いていた場合、変換ケーブルを買うのは**不可**です
    （嵌合体が約 14×7×8mm と大きく、筐体の左ポケットの JST の置き場所（長さ 約11mm まで）に入りません）。
- **買ってはいけない例**: 千石電商 DTP652533（6.5×25×33mm）は**長さ33mmが筐体に入りません**。
- **届いたら真っ先にやること**: テスターのDC電圧レンジで電圧を測り、**どちらのリードが＋か**を確認。
  **中国製セルには赤黒が逆に付いている個体、さらにコネクタのハウジング内で
  コンタクトの位置が逆になっている個体が実在します。**
  **色もコネクタの形も信用しないでください。**
  このガイドでは「セルを嵌合した状態でピグテールの線の先の電圧を測り、＋を示した線を BAT+ に
  はんだ付けする」順序にして、色にもハウジングにも依存しないようにしています
  （[手順5](#手順5-電池ピグテールjstの準備と極性の測定はんだ-0か所) と [手順8](#手順8-電池をつなぐjstコネクタ-最重要)）。
  **電池のプラグの穴にテスターの棒を直接当てて測ることはしません**（ショートの危険。§0）。

### 5.3 【重要】microSDカードの買い方

- **32GB以下**を買ってください。**Seeed公式wikiのサポート上限が32GB**です。
- **FAT32でフォーマット**して使います。32GBまでは出荷時からFAT32なのでそのまま使えます。
- 64GB以上は出荷時 **exFAT** なので FAT32 への再フォーマットが必要ですが、
  **Windows標準機能では32GB超をFAT32にフォーマットできません**（`guiformat` などの外部ツールが要る）。
  初心者は素直に32GBを選んでください。
- Class10 / UHS-I (U1) 以上。SanDisk・Samsung・KIOXIA など素性のわかるメーカー品を。
  極端に安いノーブランド品は容量偽装・書き込み中の脱落があります。

### 5.4 そのほかの注意

- **磁石は「φ6mm × 厚2mm」を4個**。厚3mmや径8mmを買うと筐体のポケットに入りません。
- **接着剤は瞬間接着剤を使わないでください**（磁石とLED窓の固定）。
  瞬間接着剤は硬化時に白い曇り（ブルーム）を出し、**LEDのレンズと窓の内側を曇らせます**。
  また磁石の固定では、剥がすときの引き剥がし方向の力に瞬間接着剤は弱く、磁石が抜けます。**2液エポキシ**を使ってください。
- 抵抗とLEDは袋売り（100本入りなど）になることが多いので、単価と実際の支払額は違います。

---

## 6. 3Dプリント手順

### 6.1 どのファイルを印刷するか

作るバリアントに合わせて、**body / lid / backplate の3つのSTLをすべて1個ずつ**印刷します。
**カバンのショルダーストラップに付けたい場合は strapplate も印刷します**（服に付ける裏板と使い分け。[手順12](#手順12-カバンのストラップに付ける任意)）。
**スマホの背面（MagSafe）に付けたい場合は magsafeplate も印刷します**（[手順13](#手順13-スマホの背面magsafeに付ける任意v110)）。

```
allday を作る → stl/allday/mindclip_body.stl
                stl/allday/mindclip_lid.stl
                stl/allday/mindclip_backplate.stl
                stl/allday/mindclip_strapplate.stl   ← カバン用（任意）
                stl/allday/mindclip_magsafeplate.stl ← スマホ背面用（任意）

slim を作る  → stl/slim/mindclip_body.stl
                stl/slim/mindclip_lid.stl
                stl/slim/mindclip_backplate.stl
                stl/slim/mindclip_strapplate.stl     ← カバン用（任意）
                stl/slim/mindclip_magsafeplate.stl   ← スマホ背面用（任意）
```

> **以前の版の筐体を印刷済みの人へ（v1.11）**: **body（本体）と lid（フタ）は刷り直してください。**
> v1.11 で残りの実測値（JST コネクタ・LED・マイクの位置・XIAO の厚み）を反映し、**body と lid の両方が変わりました**
> （マイク穴が 1.9mm 左へ、LED の窓が 1.6mm 左へ、LED の筒の深さ、slim は奥行き +0.1mm）。
> **v1.10 までに印刷した body / lid は、どの版のものも使えません。** backplate・strapplate・magsafeplate は v1.10 と同一データです。
> （その前の v1.8 では外形の幅が 39.0 → 40.0mm に変わっています。v1.7 以前の body / lid には電池が入りません。）
>
> | 部品 | 以前の印刷物は使えるか |
> |---|---|
> | **body** | **使えない。刷り直し**（v1.11 でマイク穴 3つの位置が変わった。slim は奥行きも +0.1mm。v1.10 以前の body はすべて刷り直し） |
> | **lid** | **使えない。刷り直し**（v1.11 で LED の窓が 1.6mm 左へ移動し、筒の深さも変わった。v1.10 以前の lid はすべて刷り直し） |
> | **strapplate**（カバン用・任意） | **v1.8 以降のものは使える**（v1.11 でも同一データ。v1.7 のものは本体の幅に合わず使えない） |
> | **magsafeplate**（スマホ背面用・任意） | **使える**（v1.10 で追加。v1.11 でも同一データ） |
> | **backplate**（裏板） | **使える**（最初の版から 1 バイトも変わっていない同一データ） |
>
> LED は allday / slim のどちらも、ドーム先端がフタ面の 0.2mm 内側に沈みます（slim が 0.5mm 出ていたのは v1.7 までの話です）。

STLが無い／パラメータを変えたい場合は、CadQuery 2.8 が入った環境で以下を実行すると再生成されます。

```bash
cd hardware
python3 cad/mindclip_case.py                        # allday（既定）
MINDCLIP_VARIANT=slim python3 cad/mindclip_case.py  # slim
# strapplate を自分のストラップに合わせる（MEASUREMENTS.md の M7 で測った幅・厚み）
MINDCLIP_STRAP_W=32 MINDCLIP_STRAP_T=2.0 python3 cad/mindclip_case.py
```

### 6.2 材料は PETG

**PETG を使ってください。** 理由は3つあります。

- **PLA は不可**: 夏の車内・直射日光下（60℃前後）で軟化して変形します。体温に触れる装着品なので避けます。
- **ABS は反りやすく**、この大きさの薄肉部品では寸法が出にくい（スナップフィットが合わなくなる）。
- PETG は耐熱（ガラス転移温度 約80℃）・靭性ともに十分で、**スナップフィットのたわみに耐えます**。

**色は黒（できればマット）がおすすめです。** 光沢やロゴがないだけで「何かのガジェット」以上には見られにくくなり、
沈めた LED の窓も黒地の中の小さな穴にしか見えません。

### 6.3 推奨スライサ設定

| 項目 | 値 |
|---|---|
| ノズル径 | **0.4 mm** |
| 積層ピッチ（レイヤー高さ） | **0.2 mm** |
| 壁（外周）の周回数 | **4周（= 1.6mm）**（最低でも3周） |
| インフィル（中身の充填率） | **30%**（グリッド or ジャイロイド） |
| ノズル温度 | 235〜245℃（フィラメントの指定に従う） |
| ベッド温度 | 70〜80℃ |
| 印刷速度 | 40〜50 mm/s（小さい部品なので速くしない） |
| 冷却ファン | 30〜50%（PETGは強く冷やすと層間が弱くなる） |
| **サポート** | **3部品とも不要** |
| ブリム | 迷ったら付ける（PETGは反りにくいが、接地面積が小さい lid で保険になる） |
| シーム位置 | 「後方」または「コーナー」に。背面（服に当たる面）に来るようにする |

**壁4周（1.6mm）にする理由**: 筐体の標準壁厚が1.6mmなので、4周にするとインフィルなしの完全ソリッド壁になり、
USB-Cケーブルの抜き差しの力やスナップの繰り返し開閉に対して強くなります。

### 6.4 印刷する向き（重要）

| パーツ | ベッドに接する面 | サポート | 理由 |
|---|---|---|---|
| **body**（本体） | **背面（服に当たる、平らな面）を下に**。開口している側が上を向く | 不要 | 内部のリブがすべて床から立ち上がる形になり自己支持する。USB開口の上辺 約10mm はブリッジになるが、PETGなら問題ない長さ |
| **lid**（フタ） | **外面（表に見える化粧面）を下に**。lip（スカート）と押さえリブが上を向く | 不要 | 表に出る面が一番きれいに出る。スナップリッジは半円断面なので自己支持する |
| **backplate**（裏板） | **肌に当たるフラットな面を下に**（磁石ポケットが上を向く） | 不要 | ベッド面がそのまま肌当たり面になり、最も滑らかに仕上がる |
| **strapplate**（カバン用・任意） | **ストラップに当たる平らな面を下に**（リムと磁石ポケットが上を向く） | 不要 | スロットは縦の貫通穴、ポケットは上が開いた凹みなので、ブリッジもオーバーハングも出ない |

**4つとも（strapplate を含む）「サポートなし」で設計されています。** スライサが自動でサポートを付ける設定になっていたら、**オフにしてください**
（内部にサポートが生成されると、除去できずに部品が入らなくなります）。

### 6.5 印刷前のテスト印刷（強く推奨）

いきなり本体を印刷せず、**まず backplate（裏板・約2.9g・15分程度）だけ印刷**してください。
これで確認できることが2つあります。

1. **磁石が φ6.2mm のポケットに入るか。** FDMの穴は設計値より 0.1〜0.3mm 小さく出ます。
   きつくて入らない場合は、`cad/mindclip_case.py` の `MAG_FIT = 0.2` を **0.3** にして再生成するか、
   丸の針ヤスリでポケットを軽く広げてください。
2. あなたのプリンタの寸法精度そのもの。

### 6.6 印刷後の後処理

- ブリムを付けたら丁寧に剥がし、縁のバリをデザインナイフで取る。
- **body のスナップ受け溝（内壁の水平な半円の溝、左辺2か所・下辺2か所・右辺1か所）**は、
  内部オーバーハングなので表面が荒れます。**丸い針ヤスリで軽くさらって**おくと嵌合が安定します。
- 糸引き（ストリング）はPETGでは出やすいので、ピンセットで取り除く。
- **リッドの嵌め合いを空の状態で確認**します。
  - **きつくて入らない** → `CLR = 0.15` を `0.20` にして再印刷、または lip の外面を紙ヤスリで軽く削る
  - **ゆるくてパチンとしない／すぐ開く** → `CLR` を `0.10` に、または `SNAP_PROTRUDE = 0.3` を `0.4` にして再印刷
  - **初回で一発で決まらないのは想定内です**（[§9](#9-既知の課題未検証事項)参照）。調整を前提に、最初は body と lid だけ刷って試すのも手です。

---

## 7. 組み立て手順

### 7.1 全体の流れ

```
手順1  磁石を接着する（エポキシの硬化に時間がかかるので最初にやる）
  ↓
手順2  XIAO の準備（カメラを外す／拡張ボードの確認）
  ↓
手順3  LEDサブアセンブリを作る          … はんだ 3か所
手順4  スイッチ + GNDデイジーチェーン    … はんだ 2か所
手順5  電池ピグテール(JST)の線を切りそろえる → 極性を測る
                                      … はんだ 0か所（切る・剥く間、電池は袋の中）
手順6  XIAO に3本の線をはんだ付けする    … はんだ 3か所
  ↓
手順7  【電池を繋ぐ前に】USB給電で動作確認 → §8 のテスト1〜4
  ↓
手順8  ピグテールをXIAOにはんだ付け→テスタゲート→電池を嵌合
                                      … はんだ 2か所（★最重要）
  ↓
手順9  絶縁処理
  ↓
手順10 筐体に組み込む
  ↓
手順11 装着確認
                                      はんだ付け 合計 10か所
```

> **v1.5（構成 A-1）での変更点** — 古い作例と混ざらないように、ここだけ先に押さえてください。
>
> | | v1（旧） | **v1.5（このガイド）** |
> |---|---|---|
> | 電池の接続 | XIAO 裏面パッドへ**直はんだ**（充電済みセルを持ったまま） | **JST コネクタ（1.25mm 2ピン）で嵌合**。基板にはんだ付けするのは**無通電のピグテール** |
> | GND | 黒線3本を空中でより合わせる分岐点（手順5） | **デイジーチェーン**（XIAO GND → スイッチ左端端子 → LED カソード）。**分岐点は廃止** |
> | はんだ | 11か所 | **10か所**（空中3本より合わせ 0か所。線が太いピグテールで継ぎ足す場合のみ +2） |
> | ピグテールの線 | — | **長さ違い（約60 / 65mm）に切ってそのまま使う**（手順5。採用品の線は外径 0.90mm で XIAO の下を通せる。v1.8〜v1.10 の「AWG28 への継ぎ足し」は v1.11 で廃止） |
> | 必須ゲート | （なし） | **手順8-B のテスタ4項目**。1つでも不一致なら嵌合しない |
>
> 正本は [`pcb/SCHEMATIC.md`](pcb/SCHEMATIC.md) §1.4（はんだ点）と §5（電池系）です。

### 7.2 はんだ付けの基本（未経験の人はここを先に読む）

はんだ付けは「はんだをこてで溶かして垂らす」作業では**ありません**。
**部品と配線を先に温めて、そこにはんだを触れさせて吸い込ませる**作業です。

**基本の4ステップ**

1. こての温度を **320〜350℃**（鉛入りはんだの場合）にして、こて先に少量のはんだを乗せる（＝こて先メッキ）。
2. **こて先を「はんだ付けしたい2つのもの（例: パッドと電線）」の両方に同時に当てて 1〜2秒温める。**
3. そのまま**はんだを、こて先ではなく温めた部分に**当てる。スッと溶けて流れ込む。
4. はんだを離し、**その0.5秒後にこてを離す**。冷えるまで（2〜3秒）動かさない。

**良いはんだ付け**: 富士山のようななだらかな裾を持つ、光沢のある形。
**悪いはんだ付け（イモはんだ）**: 球状に盛り上がって光沢がない。→ 温度不足か、温めずにはんだだけ垂らした証拠。
吸い取り線で取り除いてやり直します。

**練習を勧めます。** 余った電線同士を3〜4回つないでみてから本番に入ってください。捨てる部品で練習するのが一番の近道です。

**共通のリカバリ方法**

| 症状 | 対処 |
|---|---|
| はんだが盛りすぎ／隣とくっついた（ブリッジ） | **はんだ吸い取り線（T4）**を患部に当て、その上からこてを押し当てる。はんだが吸い取り線に吸われる |
| はんだが玉になって乗らない | 温度不足かパッドの酸化。フラックス（T14）を塗り、こてを1〜2秒長く当てる |
| 電線が抜けた | 芯線を撚り直し、予備はんだをしてからやり直す |
| 部品を焦がした・溶かした | 部品は数十円なので**迷わず新品に交換**する（特にスライドスイッチは熱で樹脂が溶けて接点がずれる） |

### 手順1: 磁石を接着する

**必要なもの**: 印刷したbody・backplate、ネオジム磁石4個、2液エポキシ、マスキングテープ、つまようじ

1. **極性合わせが最重要です。** 4個の磁石を「本体用2個」「裏板用2個」に分けます。
   紙を1枚挟んで、**引き合う（くっつく）向き**の組み合わせを作り、上を向いている面にマスキングテープで
   印（本体側は「B」、裏板側は「P」など）を付けます。
   **左右2組とも同じ向きに揃えてください。片方だけ逆だと反発して固定できません。**
2. 2液エポキシを混ぜ、つまようじでポケットの底に少量塗ります。
3. body の磁石ポケット（電池が載る床、丸いボスの上面に開いている2つの穴）に、印を上にして磁石を押し込みます。
   **磁石の上面がポケットの縁より沈むこと**（面一以下）を確認してください。飛び出していると電池が浮きます。
4. backplate も同様に、**磁石ポケットが開いている側**（服に当たる側）から押し込みます。
   反対側（肌に当たる面）は完全にフラットです。
   - **裏板側は特に接着を丁寧に。** 服から外すときに磁石を引き剥がす方向の力がかかるので、
     接着が甘いと磁石だけ抜けます。ポケット底面にしっかり接着剤を行き渡らせてください。
5. **硬化を待ちます**（5分硬化型でも実用強度までは30分〜数時間、説明書に従う）。この間に手順2〜6を進めます。

> **やってはいけないこと**: 瞬間接着剤の使用（引き剥がし力に弱く、硬化ガスで筐体内が白く曇る）。
> 磁石をポケットから飛び出させて接着すること（電池が浮いてリッドが閉まらなくなる）。

### 手順2: XIAO の準備

1. XIAO ESP32S3 Sense の箱には、**メイン基板**と**Sense拡張ボード**（マイクとmicroSDスロットが載った板）、
   そして**カメラモジュール**（フレキシブルケーブル付き）が入っています。
2. **拡張ボードは、はんだ付け不要です。** メイン基板の裏にある B2B コネクタ（黒い小さなコネクタ）に、
   位置を合わせて**まっすぐ「カチッ」と押し込むだけ**です。斜めに押すとピンが曲がります。
   - **向きに注意**: 拡張ボードは**部品面（USB-Cコネクタがある側）に**装着します。
     結果として、**BAT+/− のはんだパッドがある面が「裏面」**になります。
3. **カメラは使いません。** 拡張ボードの白いコネクタのラッチを起こして、フレキケーブルを抜き、
   カメラモジュールを取り外してください（そのままだと厚みが増えて筐体に入りません）。
   外したカメラは静電気防止袋に入れて保管を。
4. microSDカードを拡張ボードのスロットに挿しておきます（[§8](#8-動作確認) のテストで使います）。
5. **基板の端子部分（金色の部分）に素手で触らない**でください。作業前に金属に触れて静電気を逃がします。

### 手順3: LEDサブアセンブリを作る（はんだ 3か所）

LED は**フタ（lid）側に接着**され、配線で本体側の XIAO と繋がります。
フタを開け閉めするたびに配線が引っ張られるので、**配線は長めに取ります**。

**用意するもの**: 3mm赤色LED × 1、220Ω抵抗 × 1、橙の電線・黒の電線
（**allday は各 60mm / slim は各 45mm**。剥き代を入れて +5mm で切ってください）、熱収縮チューブ

> **電線の長さは「長ければ安心」ではありません。** slim は左ポケットの空きが 約1.6cm³ しかなく、
> 60mm のままだと充填率が約 50%（実用上限 50〜60% の入口）に掛かって、
> **最後にフタが閉まらない**という一番タチの悪い失敗になりやすくなります。
> slim では 45mm にしてください（充填率 約46%。そのぶんフタの開き角は狭くなります）。
> allday は 60mm で余裕があります（充填率 約44%）。

> **【重要】黒の電線は両端がはんだ付けで塞がります。**
> この黒線は「LEDのカソード」と「スイッチの左端端子」を直接つなぐ線です（v1.5 のデイジー
> チェーン。v1 にあった空中の分岐点はありません）。
> **太めの熱収縮チューブ（φ3mm、20mm長）を、はんだ付けを始める前に必ず通しておいてください。**
> 後からは絶対に通りません。

> **220Ωの見分け方**: カラーコードが **赤・赤・茶・金**（2 → 2 → ×10 → ±5%）です。
> 不安ならテスターの抵抗レンジで測って 209〜231Ω の範囲にあることを確認してください。

> **LEDの足の見分け方**: **長い足＝アノード（A、＋側）**、**短い足＝カソード（K、−側）**。
> 足を切ってしまった場合は、LEDの樹脂を覗いて**中の金属板が大きい方がカソード**、
> または**樹脂のフチが平らに削られている側がカソード**です。

1. **【はんだ #7a】220Ω抵抗の片方の足 ← 橙の電線**
   - **何を・どこに**: 抵抗の片足と、被覆を4mm剥いた橙の電線を繋ぐ。
   - **コツ**: 抵抗の足を電線にフック状に1回巻き付けてから、はんだを流す。**先に橙の電線に熱収縮チューブ（φ2〜3mm、15mm長）を通しておく**（はんだ付け後には通せません）。
   - **間違えると**: この線が後で XIAO の D3 に繋がります。順番自体を間違えることはありません。
2. **【はんだ #7b】220Ω抵抗のもう片方の足 ← LEDの長い足（アノード）**
   - **何を・どこに**: 抵抗の残った足を、LEDの**長い足**に繋ぐ。足同士を絡めてはんだ付けし、余った先はニッパーで切る。
   - **コツ**: **こてを当てる時間は3秒以内**。LEDは熱に弱く、長時間熱するとチップが死にます。ピンセットで足の付け根を挟んでおくと放熱器代わりになります。
   - **★間違えると何が起きるか**: **抵抗を入れ忘れて GPIO と LED を直結すると、電流が制限されずに LED と XIAO の GPIO ピンが壊れます。**
     この抵抗は「無くても光るが、あとで壊れる」部品ではなく、**必須の保護部品**です。
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
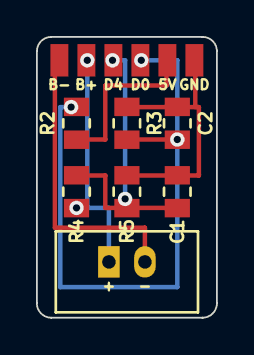
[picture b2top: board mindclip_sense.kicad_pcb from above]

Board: 2 copper layers, 10.0 x 15.6 mm, 8 parts (0 on the bottom side), 6 nets.

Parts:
C1, C2: 100nF; C_0805_2012Metric_MC
J1: JST_PH_2P; JST_PH_B2B-PH-K_1x02_P2.00mm_Vertical_MC
J2: WIRE x6; WireLand_SMD
R2, R4, R5: 220k; R_0805_2012Metric_MC
R3: 330k; R_0805_2012Metric_MC

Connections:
BATN: J1.2, J2.1
BATP: J1.1, J2.2, R4.1
GND: C1.2, C2.2, J2.6, R3.2, R5.2
VBAT_SENSE: C1.1, J2.3, R4.2, R5.1
VBUS: J2.5, R2.1
VBUS_SENSE: C2.1, J2.4, R2.2, R3.1

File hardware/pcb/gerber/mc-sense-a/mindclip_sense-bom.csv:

Comment,Designator,Footprint,LCSC Part #
"100nF","C1,C2","MindClip:C_0805_2012Metric_MC",
"220k","R2,R4,R5","MindClip:R_0805_2012Metric_MC",
"330k","R3","MindClip:R_0805_2012Metric_MC",
"JST_PH_2P","J1","MindClip:JST_PH_B2B-PH-K_1x02_P2.00mm_Vertical_MC",
"WIRE x6","J2","MindClip:WireLand_SMD",
# LCSC Part # は未指定。JLCPCB の SMT 実装を使う場合は発注前に記入すること。
# 本プロジェクトの既定は手はんだ（0805 まで）なので実装サービスは任意。

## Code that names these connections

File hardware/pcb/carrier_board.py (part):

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  VBAT_MID   Q1.S, Q2.S                      (背中合わせ FET の共通ソース)
  VBAT_SYS   Q2.D, TP1, R4.1                 (保護後。XIAO BAT+ へジャンパ)
  VBUS       U1.5V, R2.1                     (XIAO の 5V ピン = USB VBUS 直結)
  VBUS_SENSE R2.2, R3.1, C2.1, U1.D0         (GPIO1 / RTC / デジタル入力で使用)
  VBAT_SENSE R4.2, R5.1, C1.1, U1.D4         (GPIO5 / ADC1_CH4)
  SW_IN      U1.D1, J2.1                     (GPIO2 / 内部プルアップ / ON=GND)
  LED_DRV    U1.D3, R1.1                     (GPIO4)
  LED_A      R1.2, J3.1

■ 未接続 (ランドのみ・機械保持用に半田付けしてよい)
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
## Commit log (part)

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2026-06-06 fx(stock): offline --sim mode so the stock system runs with no kabuステーション
    While the auカブコム account is 審査待ち there is no account-less stock demo
    (kabuステーション's 検証環境 still needs the real app logged in). Add an offline
    simulator so the mechanics can be seen now:
    - SimKabuStation: drop-in KabuStation over a synthetic seeded random walk on real
    TSE tickers, with an in-memory margin book (buys/closes execute into it, equity
    marks to market). Opus (with a key) can pick real names against it; otherwise
2026-06-06 fx: split the /live dashboard into FX vs 信用株 (stocks) views
    /live showed only the single latest run, so FX and the stock system overwrote
    each other on the same screen — and the MT5 bridge status even leaked the FX
    position into a stock run. Fix:
    - db.latest_run_id(kind): "fx" / "stocks" filter by instrument (JP-STOCKS).
    - /api/live?kind=fx|stocks picks the latest run of that system; the MT5 bridge
    status override now applies to FX runs only.
2026-06-06 fx(stock): show real holdings on the /live 信用株 view
    The stock view's top cards were FX-shaped (position lots / trade count) and read
    empty even while holding stocks. Now:
    - run_stock_ai records a per-cycle portfolio snapshot (source="portfolio", so it
    stays out of the decision log) with each held name's qty / value / PnL.
    - /api/live returns holdings (+ risk falls back to max_risk for stock runs).
    - live.html: for the stock view the cards become 保有銘柄 (per-name P&L chips) and
2026-06-06 fx(stock): make --sim free by default; add --opus to opt into paid selection
    The sim used Opus automatically whenever a key was set, so `--sim --sim-steps 8`
    fired 8 Opus+web-search calls and could drain Anthropic credits unexpectedly.
    Now --sim always uses the free rule picker; add --opus for real Opus selection
    (one paid call per cycle). The Opus-unavailable path already fails safe (hold).
    STOCK_AI.md updated. 81 tests green.
2026-06-10 fx: add PDCA monitor — live vs backtest health check (run_monitor)
    The measurement half of the PDCA loop. Compares the live FX run's realized
    stats against the validated backtest envelope (H1/SMA2400/5x: ~12% CAGR,
    ~34% maxDD, ~20 trades/yr) and flags four failure modes early:
    - DRAWDOWN BREACH : live max DD > 34% -> edge may be breaking
    - OVERTRADING : position changes >> ~20/yr -> whipsaw/bug
    - EXECUTION DRIFT : strategy says LONG/FLAT but the live book disagrees
2026-06-10 docs(golive): criteria-based go-live checklist (~4 weeks -> live small)
    Demo's purpose is plumbing + psychology, not proving profit (a few months is
    noise for a ~20-trade/year edge). Add explicit go-live criteria (execution-match
    green, survives a weekend+event, leverage<=5x, one full cycle, can stomach the
    DD) -> then go live at minimum size and scale by funding, not leverage.
2026-06-10 fx(monitor): compare the live book to the system's DECISION, not the raw trend
    The execution-drift check compared the bare trend signal to the live position,
    so a legitimate Opus veto (trend LONG but system correctly decided FLAT) was
    mis-flagged 🔴. Now it compares the live book to the system's LAST recorded
    decision (the bare trend is shown only as context), and adds a staleness check
    (flags if the run hasn't updated in >1.5 days = possibly stopped). Fixes the
    false 'execution drift' alarm. 90 tests green.
2026-06-10 docker: containerize the Python brain so Windows Python is no longer needed
    Escape the broken/AV-clobbered Windows Python entirely: run everything in clean
    containers, with only Docker Desktop installed on Windows. MT5 (the EA) stays
    native; the fx container talks to it through MT5's shared Common\Files folder
    (mounted via MT5_COMMON_FILES_HOST).
    - Dockerfile (python:3.12-slim + requirements)
    - docker-compose.yml: dashboard (8000), fx (run_ai_bridge), and an on-demand
2026-06-10 fx: multi-currency study (research_run9) — the edge does NOT travel; stay USD/JPY-only
    User question: does trading multiple pairs lower DD / raise profit? Tested on
    real MT5 H1 data 2015-2026 (~71k bars/pair: GBPJPY, EURUSD, AUDUSD, GBPAUD),
    rule UNCHANGED (SMA2400 / risk4% / 5x / TP off), directions pre-registered by
    structure (yen pairs long-only, non-yen symmetric), realistic per-pair spreads.
    - Per pair: USDJPY +12.4%/34%DD; GBPJPY +3.7%/47%; EURUSD(L+S) -7.6%/84%;
    AUDUSD(L+S) -29.5%/99%; GBPAUD(L+S) -16.2%/94%. Failures persist across
2026-06-13 docs: add OVERVIEW.md — Notion-ready summary (overview / mechanics / run / ops)
2026-06-19 feat: remote dashboard access via Cloudflare Tunnel + Basic auth gate
    Lets the dashboard be viewed from outside with no router port-forwarding.
    Security first: the dashboard is read-only but exposes account state, so add an
    HTTP Basic auth gate (FXSIM_DASH_USER/PASS) — off when no password is set
    (local use), enforced on every route once a password is configured.
    - app/server.py: env-gated HTTP Basic dependency on all routes (auto_error=False
    so local use needs no login). Covered by tests/test_dashboard_auth.py.
2026-06-19 fx: default the live decision model to Sonnet 4.6 (cheaper veto, override via .env)
    At a ¥300k-class account Opus's fixed cost exceeds the strategy's profit;
    Sonnet keeps the AI veto in the black. Set on the fx service, overridable with
    FXSIM_DECISION_MODEL in .env.
2026-06-27 C3: 連系実オッズ評価を全テスト期間に拡張し「実オッズのみROI」を別建て集計
    これまで --real-exotic は評価年(最新年)の連系オッズしか読まず、過去テスト
    区間はすべて合成オッズにフォールバックしていた(実オッズカバー率 6/5/21%)。
    データ(NL_O2/O3/O5, 2021-2026)はDBに全て存在するため、追加取得なしで以下を改善:
    - load_exotic_odds_for_days を年単位の一括クエリ(WHERE Year=?)に変更。
    日ごと全表スキャンの旧実装より桁違いに高速。
    - 評価器が使う券種(馬連O2/ワイドO3/三連複O5)のみ読み込み、巨大な
2026-06-27 --since: 解析期間を直近に絞って高速化(WHERE Year>= でI/O削減＋学習量削減)
    5年フルの walk-forward(約35フォールド)を遅いマウント越しで回すと数時間かかる
    ため、--since YYYYMMDD で指定日以降のレースだけを解析できるようにした。
    - IngestConfig に since_year(SQL の WHERE Year>= で粗く絞りI/O削減)と
    since_ordinal(正規化後に日単位で厳密に絞る)を追加。
    - from_sqlite/from_duckdb の reader が任意の年フィルタを受け取り、レース系
    テーブル(SE/RA/O1/HR)だけ Year>= で読む(Year列の無い表は全件にフォールバック)。
2026-06-27 連系の実オッズROIにブートストラップ95%CIと的中本数を併記
    実オッズのみROIが170%等でも、的中が数本しかない連系ではその少数の高配当に
    ROIが支配され誤差が巨大になる。点推定で黒に見えても偶然と区別できない。
    ベット単位の払戻を resample して ROI の 95%CI を出し、下限が100%を超えるかで
    「控除後でも有意に黒/判定不能」を明示する。real_wins(的中本数)も併記。
2026-06-27 賢い金(中間オッズ)キャプチャ: 土日自動・容量安全の蓄積パイプライン
    唯一エビデンスのあるエッジ候補=締切直前のオッズの動き(東大 arXiv:2509.14645)を
    自前で検証するため、中間オッズを土日だけ軽量に蓄積する仕組みを追加。
    - tools/prune_realtime_odds.py: realtime取得後に単勝の時系列(TS_SOKUHO_O1)だけ
    odds_history.db へ退避し、本体の TS_SOKUHO_O1..O6 を一掃。VACUUMはしない
    (21GB DBのVACUUMは空き容量不足で危険)。空きページ再利用で本体は頭打ち。
    - scripts/weekend_capture.ps1: realtime起動→夕方kill(stopはno-op)→剪定→cache掃除。
2026-06-28 PowerShellのバックティック行継続を全廃しsplattingに(タスク登録の-UserId認識エラー修正)
    行末バックティックはエディタ/git経由で末尾空白が入ると継続が壊れ、
    -UserId 等が別コマンドと誤認されて失敗する。register/capture 両スクリプトの
    継続をハッシュテーブル渡し(splatting)と1行化に置換して堅牢化。
2026-06-28 PowerShellスクリプトを純ASCII化(PS5.1のShift-JIS誤読によるパースエラー修正)
    Windows PowerShell 5.1 はUTF-8(BOM無)の日本語コメントをShift-JISと誤読し、
    マルチバイト列がブレース/改行を飲み込んでパースを壊す(register側で
    '}'のUnexpectedToken)。両.ps1のコメント・文字列を全て英語ASCIIにして
    文字コードに依存せず必ず通るようにした。-At も "09:00" に。説明は
    docs/SMARTMONEY_CAPTURE.md とチャットに日本語で残す。
2026-06-28 剪定を実物テーブルTS_O1に修正＋1分間引き(realtimeの秒刻み再取込でTS_O1が肥大)
    実測: realtimeの単複オッズは TS_O1 に入る(TS_SOKUHO_O1ではない=空)。
    さらに数秒ごとに再取込されTS_O1が猛烈に増えるため、退避を(レース×馬番×分)
    単位に間引いて odds_history.db に積む(賢い金は秒単位不要・論文も5分刻み)。
    冪等性のためユニーク索引+INSERT OR IGNOREで前週分の再取得も重複しない。
    一掃対象を TS_O1..O6(と空のTS_SOKUHO_O1..O6)に修正。docsの確認クエリもTS_O1へ。
2026-06-28 剪定の分バケットをISO形式CollectedAtに修正(substr 1,12→1,16)
    実データの CollectedAt は ISO形式 '2026-06-27T04:59:46.016719+00:00' で、
    14桁前提の substr(,1,12) では分単位に間引けていなかった(先頭12文字が
    '2026-06-27T0' になり粒度が崩れる)。分バケット=先頭16文字に修正。
    テストも14桁の偽データからISO形式の実物に合わせて修正。
2026-06-29 剪定の時間軸をHassoTimeに修正(CollectedAtはバースト潰れで使用不可)＋実馬のみ退避
    実データ判明: 真の時間軸は HassoTime(発表時刻 MMDDHHMM, 前売り〜締切)。
    CollectedAt(取り込み時刻)は起動時の一括取込で16秒に潰れ軸にならない。
    さらに TanVote(単勝票数)が締切直前に急増=賢い金の直接信号として取れている。
    - 退避キーを (レース×馬番×HassoTime) に変更し全スナップショット=軌跡を保持
    (旧: CollectedAt分間引き → 同一16秒に潰れて軌跡を1点に破壊する致命バグ)。
    - 実馬(Umaban>0)のみ退避(Umaban=0の集計行を除外し容量約7割減)
